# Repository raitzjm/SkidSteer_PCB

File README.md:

# SkidSteer_PCB
PCB for skid steer spraying rover project for KSU Precision Ag Lab

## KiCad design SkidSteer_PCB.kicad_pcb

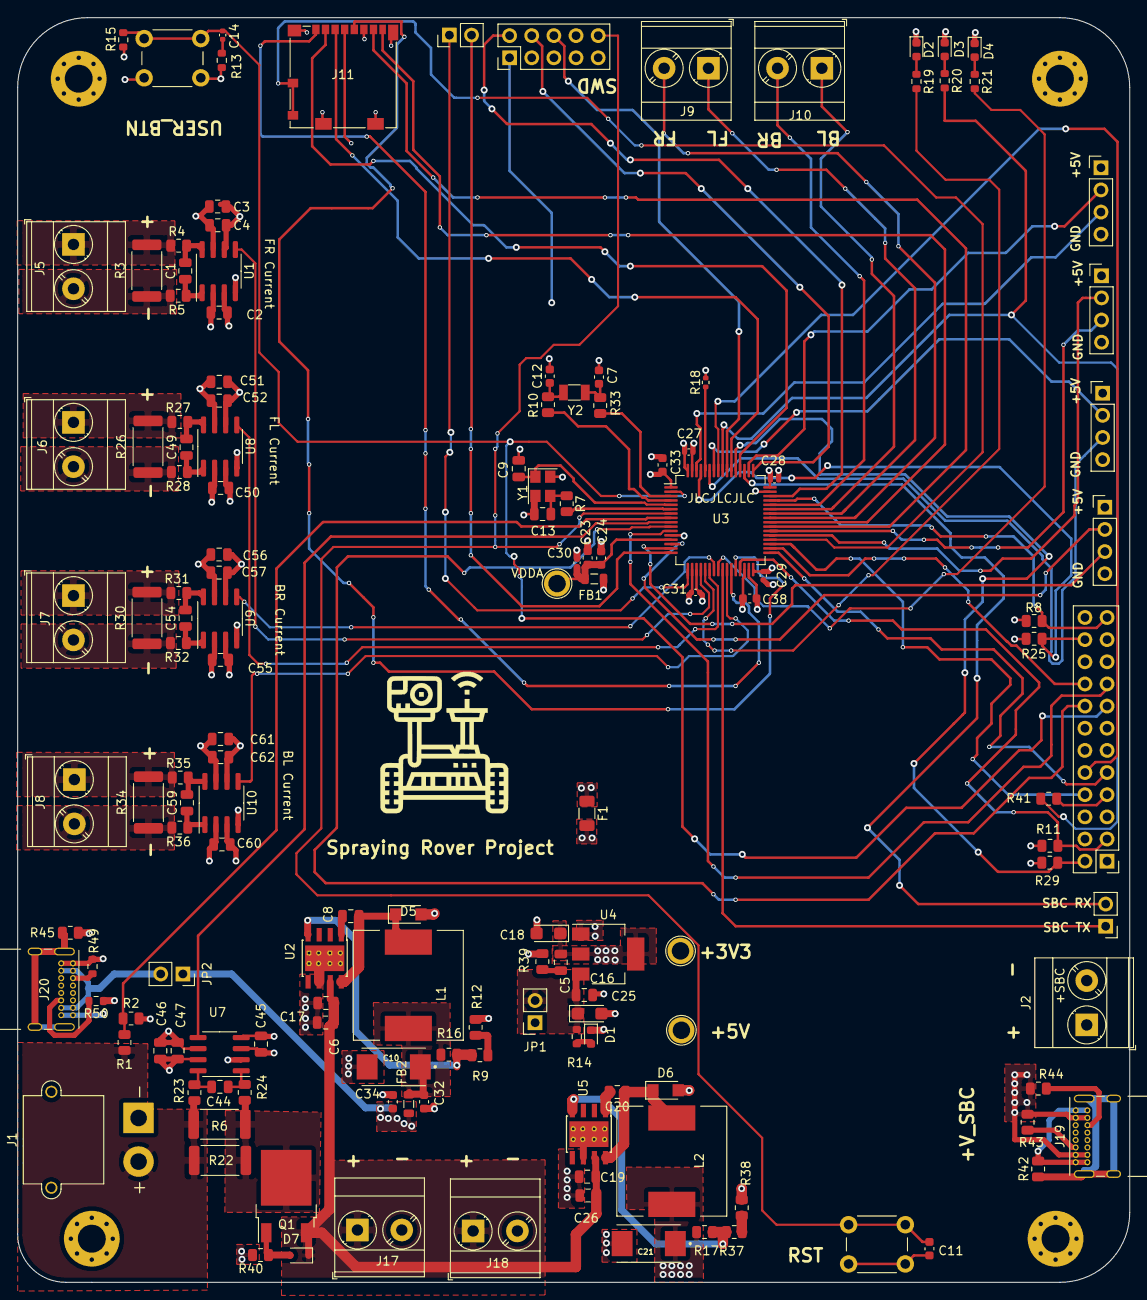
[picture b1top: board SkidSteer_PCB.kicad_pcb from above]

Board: 4 copper layers, 127.5 x 145.0 mm, 152 parts (0 on the bottom side), 107 nets.

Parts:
C1, C17, C26, C44, C49, C54, C59: DNU; C_0805_2012Metric
C2, C4, C45, C47, C50, C52, C55, C57, C60, C62: 0.1uF; C_0805_2012Metric
C3, C46, C51, C56, C61: 10uF; C_0805_2012Metric
C5: 22u; C_0805_2012Metric
C6, C16, C19: 10u; C_0805_2012Metric
C7, C12: 15pF; C_0603_1608Metric
C8, C20: 10nF; C_0805_2012Metric
C9, C13: 30p; C_0805_2012Metric
C10, C21: 6TPB330M; CAP_6TPB330M
C11: 100nF; C_0603_1608Metric
C14, C27, C28, C29, C30, C31: 100nF; C_0402_1005Metric
C18, C25: DNU; CP_EIA-3216-18_Kemet-A
C23, C32, C34: 1u; C_0603_1608Metric
C24: 10n; C_0603_1608Metric
C33: 1uF_X5R_0603; C_0603_1608Metric
C38: 2.2uF_X7R; C_0603_1608Metric
D1: RED; LED_0603_1608Metric
D2: Blue; LED_0603_1608Metric
D3: Red; LED_0603_1608Metric
D4: Green; LED_0603_1608Metric
D5, D6: S3P6R; D_SMF
D7: 10V; D_SOD-323
F1: 300mA; Fuse_1206_3216Metric
FB1: 600 @ 100 Mhz; L_0805_2012Metric
FB2: 100R; L_0805_2012Metric
H1, H2, H3, H4: MountingHole_Pad; MountingHole_3.2mm_M3_Pad_Via
J1: Conn_01x02; AMASS_XT30PW-M_1x02_P2.50mm_Horizontal
J2: Conn_01x02; TerminalBlock_Phoenix_MKDS-3-2-5.08_1x02_P5.08mm_Horizontal
J3, J21: Conn_01x02; PinHeader_1x02_P2.54mm_Vertical
J4: Conn_02x12_Counter_Clockwise; PinHeader_2x12_P2.54mm_Vertical
J5, J6, J7, J8, J9, J10, J17, J18: Screw_Terminal_01x02; TerminalBlock_Phoenix_MKDS-3-2-5.08_1x02_P5.08mm_Horizontal
J11: Micro_SD_Card_Det; microSD_HC_Molex_104031-0811
J12: SWD; PinHeader_2x05_P2.54mm_Vertical
J13, J14, J15, J16: Conn_01x04_Male; PinHeader_1x04_P2.54mm_Vertical
J19, J20: USB_C_Receptacle_USB2.0; USB_C_Receptacle_GCT_USB4085
JP1: BatteryPower; PinSocket_1x02_P2.54mm_Vertical
JP2: USB Power; PinSocket_1x02_P2.54mm_Vertical
L1, L2: 15uH; L_12x12mm_H8mm
Q1: SUD09P10-195; TO-252-2
R1: 150k; R_0805_2012Metric
R2: 20k; R_0805_2012Metric
R3, R6, R22, R26, R30, R34: 1m; R_2512_6332Metric
R4, R5, R7, R10, R12, R23, R24, R27, R28, R31, R32, R33, R35, R36, R38, R42: 0; R_0805_2012Metric
R8, R25, R41, R45: DNU; R_0805_2012Metric
R9, R37: 3.3k; R_0805_2012Metric
R11, R29: 4k7; R_0805_2012Metric
R13, R19: 100; R_0603_1608Metric
R14, R20, R21: 680; R_0603_1608Metric
R15: 4.7k; R_0603_1608Metric
R16, R17, R43, R44: 10k; R_0805_2012Metric
R18: 10K; R_0402_1005Metric
R39: 100; R_0805_2012Metric
R40: 1.2k; R_0805_2012Metric
R49, R50: 5.1k; R_0603_1608Metric
SW1, SW2: SW_Push; SW_PUSH_6mm
TP2: +5V; TestPoint_Plated_Hole_D2.0mm
TP4: +3V3; TestPoint_Plated_Hole_D2.0mm
TP5: VDDA; TestPoint_Plated_Hole_D2.0mm
U1, U7, U8, U9, U10: INA240A3D; SOIC-8_3.9x4.9mm_P1.27mm
U2, U5: TPS5430DDA; TI_SO-PowerPAD-8_ThermalVias
U3: STM32F446RETx; LQFP-64_10x10mm_P0.5mm
U4: NCP1117-3.3_SOT223; SOT-223-3_TabPin2
Y1: 12Mhz; Crystal_SMD_3225-4Pin_3.2x2.5mm
Y2: 32.768; Crystal_SMD_3215-2Pin_3.2x1.5mm

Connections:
+3V3: C2.1, C3.1, C4.1, C5.1, C18.1, C45.1, C46.1, C47.1, C50.1, C51.1, C52.1, C55.1, C56.1, C57.1, C60.1, C61.1, C62.1, F1.2, J4.14, J4.21, J4.24, J11.4, R8.1, R11.1, R15.2, R25.2, R29.2, TP4.1, U1.3, U1.6, U4.2, U7.3, U7.6, U8.3, U8.6, U9.3, U9.6, U10.3, U10.6
+5V: C34.1, FB2.1, J4.13, J4.19, J4.20, J13.1, J14.1, J15.1, J16.1, JP1.1, JP2.1, TP2.1
+BATT: J1.2, R1.2, R6.1, R22.1, R23.2
/BatterySensor/I_Load: Q1.2, R6.2, R22.2, R24.1
CAN1_RX: J4.23, R8.2, U3.45
CAN1_TX: J4.22, R25.1, U3.61
GND: C2.2, C3.2, C4.2, C6.2, C7.2, C9.2, C10.2, C11.2, C12.2, C13.2, C16.2, C17.2, C18.2, C19.2, C21.2, C23.2, C24.2, C25.2, C26.2, C27.2, C28.2, C29.2, C30.2, C31.2, C32.2, C33.2, C34.2, C38.2, C45.2, C46.2, C47.2, C50.2, C51.2, C52.2, C55.2, C56.2, C57.2, C60.2, C61.2, C62.2, D1.1, D2.1, D3.1, D4.1, D5.2, D6.2, H1.1, H2.1, H3.1, H4.1, J1.1, J2.2, J4.1, J4.4, J4.5, J4.6, J4.11, J4.12, J11.6, J11.11, J12.3, J12.5, J12.9, J13.4, J14.4, J15.4, J16.4, J17.2, J18.2, J19.A1, J19.A12, J19.B1, J19.B12, J20.A1, J20.A12, J20.B1, J20.B12, R2.1, R12.2, R13.1, R18.2, R38.2, R39.2, R40.2, R42.2, R45.2, R49.2, R50.1, SW1.1, SW2.2, U1.2, U1.4, U1.7, U2.6, U2.9, U3.12, U3.18, U3.31, U3.47, U3.63, U4.1, U5.6, U5.9, U7.2, U7.4, U7.7, U8.2, U8.4, U8.7, U9.2, U9.4, U9.7, U10.2, U10.4, U10.7, Y1.2, Y1.4
HSE_OSC_IN: C9.1, U3.5, Y1.1
HSE_OSC_OUT: R7.1, U3.6
I2C2_SCL: J4.3, R11.2, U3.29
I2C2_SDA: J4.2, R29.1, U3.53
LSE_OSC_IN: R33.1, U3.3
LSE_OSC_OUT: R10.1, U3.4
MotorBL+: J8.1, R34.1, R35.2
MotorBL-: J8.2, R34.2, R36.1
MotorBR+: J7.1, R30.1, R31.2
MotorBR-: J7.2, R30.2, R32.1
MotorFL+: J6.1, R26.1, R27.2
MotorFL-: J6.2, R26.2, R28.1
MotorFR+: J5.1, R3.1, R4.2
MotorFR-: J5.2, R3.2, R5.1
NRST: C11.1, J12.10, SW1.2, U3.7
unnamed: C1.1, R4.1, U1.8
unnamed: C1.2, R5.2, U1.1
unnamed: C5.2, R39.1
unnamed: C7.1, R33.2, Y2.1
unnamed: C8.1, D5.1, L1.1, U2.8
unnamed: C8.2, U2.1
unnamed: C10.1, C32.1, FB2.2, L1.2, R16.1
unnamed: C12.1, R10.2, Y2.2
unnamed: C13.1, R7.2, Y1.3
unnamed: C14.1, R13.2
unnamed: C16.1, C25.1, JP1.2, R14.1, U4.3
unnamed: C20.1, D6.1, L2.1, U5.8
unnamed: C20.2, U5.1
unnamed: C44.1, R23.1, U7.8
unnamed: C44.2, R24.2, U7.1
unnamed: C49.1, R27.1, U8.8
unnamed: C49.2, R28.2, U8.1
unnamed: C54.1, R31.1, U9.8
unnamed: C54.2, R32.2, U9.1
unnamed: C59.1, R35.1, U10.8
unnamed: C59.2, R36.2, U10.1
unnamed: D1.2, R14.2
unnamed: D2.2, R19.1
unnamed: D3.2, R20.1
unnamed: D4.2, R21.1
unnamed: D7.2, Q1.1, R40.1
unnamed: J4.7, R41.1
unnamed: J19.A5, R43.2
unnamed: J19.B5, R44.2
unnamed: J19.S1, R42.1
unnamed: J20.A4, J20.A9, J20.B4, J20.B9, JP2.2
unnamed: J20.A5, R49.1
unnamed: J20.B5, R50.2
unnamed: J20.S1, R45.1
unnamed: R9.2, R12.1
unnamed: R9.1, R16.2, U2.4
unnamed: R17.2, R37.1, U5.4
unnamed: R18.1, U3.60
unnamed: R19.2, U3.21
unnamed: R21.2, U3.24
unnamed: R37.2, R38.1
PB4: R20.2, R41.2, U3.56
PB5: J4.10, U3.57
PB14: J4.8, U3.35
PC13: C14.2, J4.15, R15.1, SW2.1, U3.2
SCB_RX: J21.2, U3.51
SCB_TX: J21.1, U3.25
SDIO_CK: J11.5, U3.28
SDIO_CMD: J11.3, U3.54
SDIO_D0: J11.7, U3.39
SDIO_D1: J11.8, U3.40
SDIO_D2: J11.1, U3.27
SDIO_D3: J11.2, U3.52
SD_Detect: J11.9, J11.10, U3.36
SPI2_MISO: J4.16, U3.10
SPI2_MOSI: J4.17, U3.11
SPI2_SCK: J4.18, U3.34
STLK_RX: J3.2, U3.16
STLK_TX: J3.1, U3.17
SWO: J12.6, U3.55
TCK: J12.4, U3.49
TMS: J12.2, U3.46
USART3_CLK: J4.9, U3.33
VBAT: C27.1, C28.1, C29.1, C31.1, C33.1, C38.1, F1.1, FB1.2, J12.1, U3.1, U3.19, U3.30, U3.32, U3.48, U3.64
VCC: C6.1, C17.1, C19.1, C26.1, D7.1, J17.1, J18.1, Q1.3, U2.7, U5.7
VDDA: C23.1, C24.1, C30.1, FB1.1, TP5.1, U3.13
VDD_SBC: C21.1, J2.1, J19.A4, J19.A9, J19.B4, J19.B9, L2.2, R17.1, R43.1, R44.1
currentBattery: U3.9, U7.5
currentMotorBL: U3.26, U10.5
currentMotorBR: U3.23, U9.5
currentMotorFL: U3.22, U8.5
currentMotorFR: U1.5, U3.20
encoderAMotorBL: J16.2, U3.14
encoderAMotorBR: J15.2, U3.58
encoderAMotorFL: J14.2, U3.37
encoderAMotorFR: J13.2, U3.50
encoderBMotorBL: J16.3, U3.15
encoderBMotorBR: J15.3, U3.59
encoderBMotorFL: J14.3, U3.38
encoderBMotorFR: J13.3, U3.62
pwmMotorBL: J10.1, U3.43
pwmMotorBR: J10.2, U3.44
pwmMotorFL: J9.1, U3.42
pwmMotorFR: J9.2, U3.41
voltageBattery: R1.1, R2.2, U3.8

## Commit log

2021-12-23 Untracked files issue resolved to fix .gitignore
2024-02-25 Delete SkidSteer_PCB-cache-DESKTOP-T2K0LP5.lib
    Delete cache files
2024-02-25 Delete fp-info-cache-MacBook Pro
    delete cache files
2024-02-25 Delete fp-info-cache-MacBook Pro-2
    delete cache files
